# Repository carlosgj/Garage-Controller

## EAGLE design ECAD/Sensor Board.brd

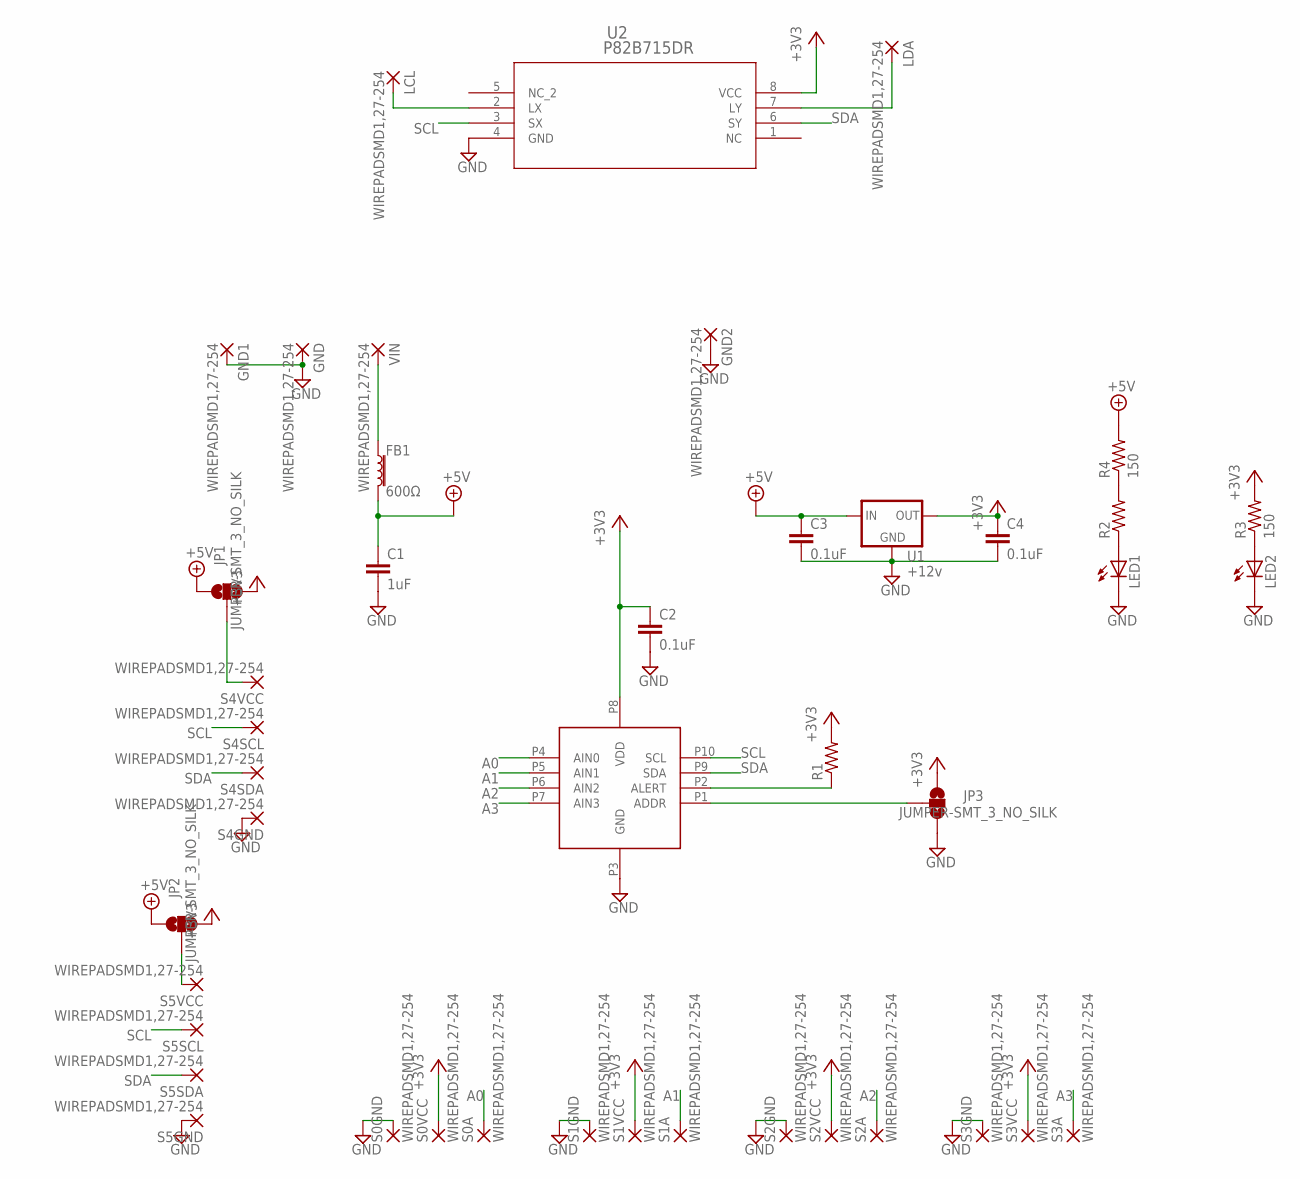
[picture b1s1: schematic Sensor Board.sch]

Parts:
C1: 1uF; C0805
C2, C3, C4: 0.1uF; C0805
FB1: 600Ω; 0805
GND, GND1, GND2: WIREPADSMD1,27-254; SMD1,27-2,54
JP1, JP2, JP3: JUMPER-SMT_3_NO_SILK; SMT-JUMPER_3_NO_SILK
LCL: WIREPADSMD1,27-254; SMD1,27-2,54
LDA: WIREPADSMD1,27-254; SMD1,27-2,54
LED1, LED2: LEDCHIP-LED0805; CHIP-LED0805
R1, R2: R-US_R0805; R0805
R3, R4: 150; R0805
S0A, S0GND, S0VCC, S1A, S1GND, S1VCC, S2A, S2GND, S2VCC, S3A, S3GND, S3VCC, S4GND, S4SCL, S4SDA, S4VCC, S5GND, S5SCL, S5SDA, S5VCC: WIREPADSMD1,27-254; SMD1,27-2,54
U1: +12v; TO-252
U2: P82B715DR; SO-08
U3: ADS1115; VSSOP-10
VIN: WIREPADSMD1,27-254; SMD1,27-2,54

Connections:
+3V3: C2.1, C4.1, JP1.3, JP2.3, JP3.1, R1.2, R3.2, S0VCC.1, S1VCC.1, S2VCC.1, S3VCC.1, U1.2 (OUT), U2.8 (VCC), U3.P8 (VDD)
+5V: C1.1, C3.1, FB1.2, JP1.1, JP2.1, R4.2, U1.1 (IN)
A0: S0A.1, U3.P4 (AIN0)
A1: S1A.1, U3.P5 (AIN1)
A2: S2A.1, U3.P6 (AIN2)
A3: S3A.1, U3.P7 (AIN3)
GND: C1.2, C2.2, C3.2, C4.2, GND.1, GND1.1, GND2.1, JP3.3, LED1.C, LED2.C, S0GND.1, S1GND.1, S2GND.1, S3GND.1, S4GND.1, S5GND.1, U1.3 (GND), U2.4 (GND), U3.P3 (GND)
unnamed: R1.1, U3.P2 (ALERT)
unnamed: FB1.1, VIN.1
unnamed: JP2.2, S5VCC.1
unnamed: JP3.2, U3.P1 (ADDR)
unnamed: JP1.2, S4VCC.1
unnamed: LED1.A, R2.1
unnamed: LED2.A, R3.1
unnamed: R2.2, R4.1
unnamed: LDA.1, U2.7 (LY)
unnamed: LCL.1, U2.2 (LX)
SCL: S4SCL.1, S5SCL.1, U2.3 (SX), U3.P10 (SCL)
SDA: S4SDA.1, S5SDA.1, U2.6 (SY), U3.P9 (SDA)

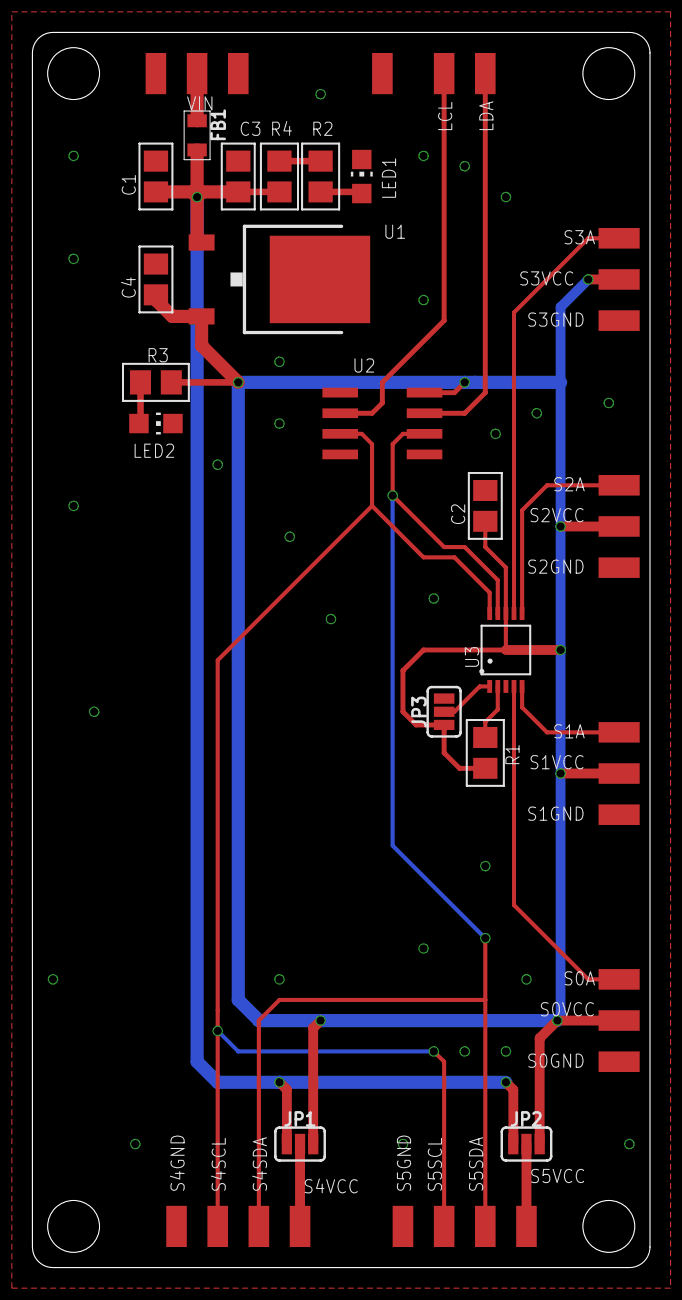
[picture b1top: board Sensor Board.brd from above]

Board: 2 copper layers, 38.1 x 76.2 mm, 43 parts (0 on the bottom side), 19 nets.

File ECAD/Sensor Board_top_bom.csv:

Comment,Designator,Footprint,LCSC Part #
,LED1 LED2,CHIP-LED0805,C84256
1k,R1,R0805,C17513
330,R2,R0805,C17630
+12v,U1,TO-252,C283274
0.1uF,C2 C3 C4,C0805,C49678
1uF,C1,C0805,C28323
150,R3 R4,R0805,C17471
ADS1115,U3,VSSOP-10,C37593
P82B715DR,U2,SO-08,C2649394

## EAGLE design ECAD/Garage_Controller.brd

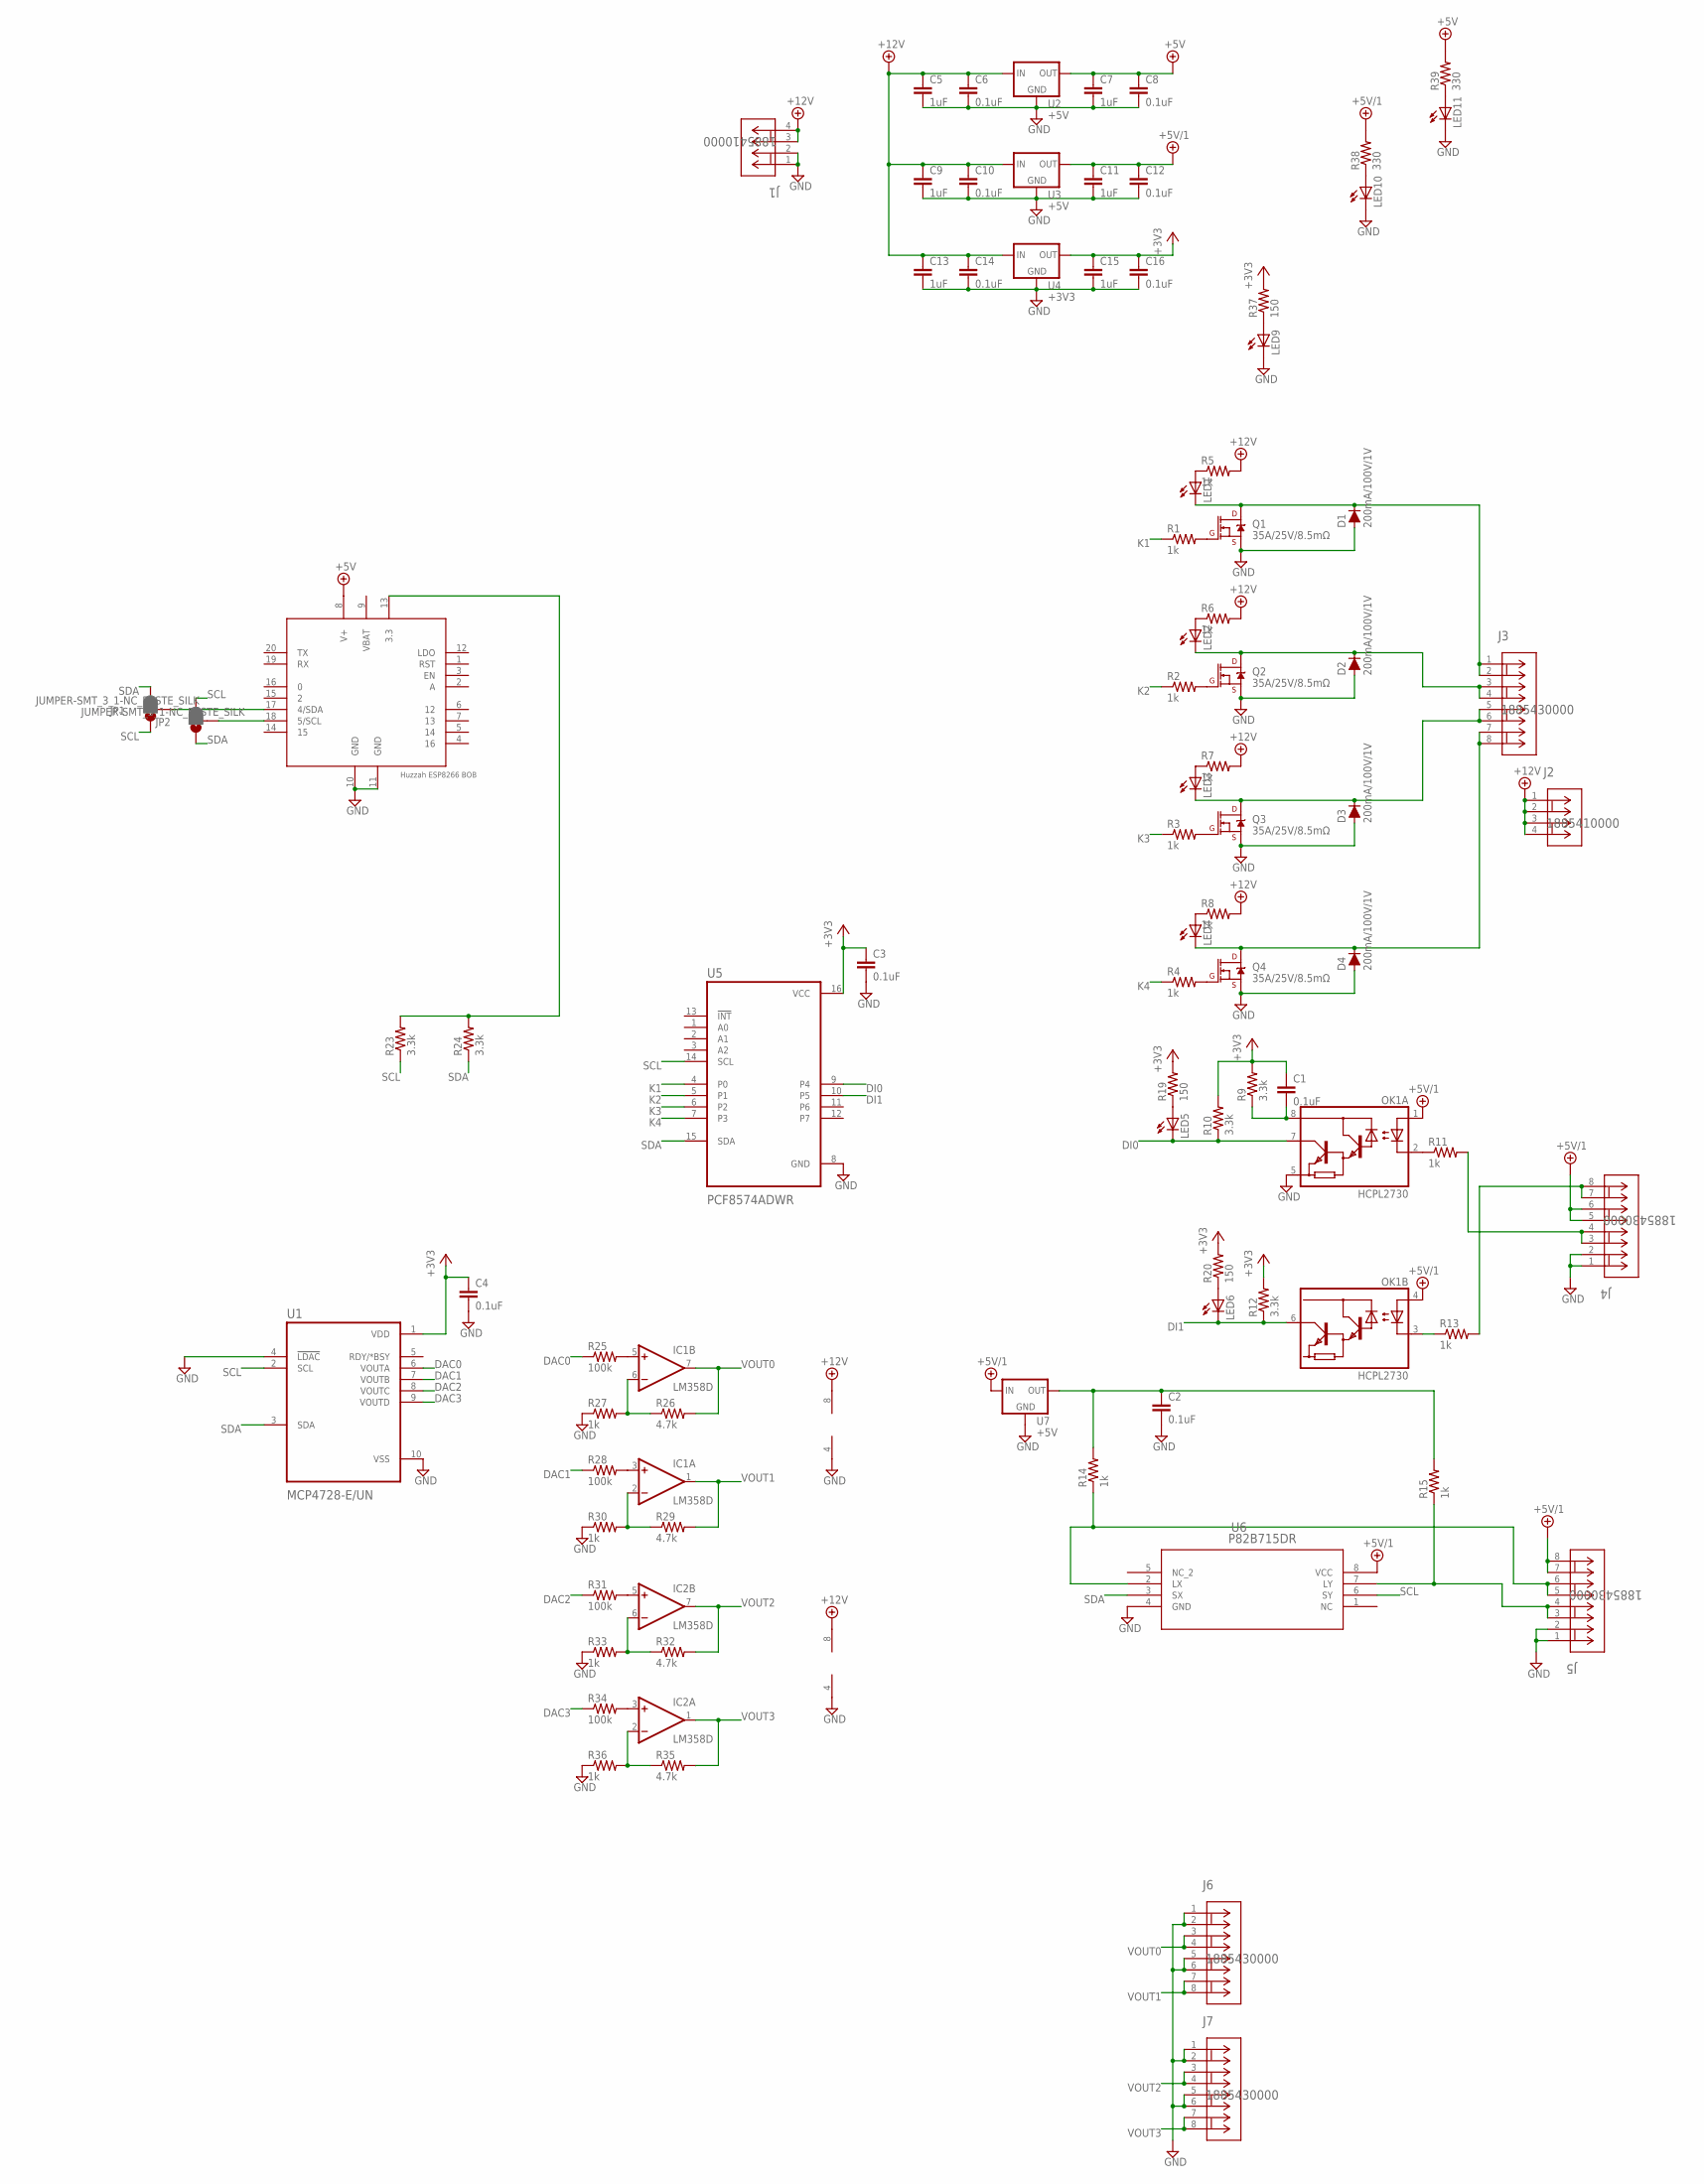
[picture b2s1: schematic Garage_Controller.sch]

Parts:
C1, C2, C3, C4, C6, C8, C10, C12, C14, C16: 0.1uF; C0805
C5, C7, C9, C11, C13, C15: 1uF; C0805
D1, D2, D3, D4: 200mA/100V/1V; DIODE-1N4148
IC1, IC2: LM358D; SO08
J1, J2: 1885410000; CONN_1885410000_WED
J3, J4, J5, J6, J7: 1885430000; CONN_1885430000_WED
JP1, JP2: JUMPER-SMT_3_1-NC_PASTE_SILK; SMT-JUMPER_3_1-NC_PASTE_SILK
LED1, LED2, LED3, LED4, LED5, LED6, LED9, LED10, LED11: LEDCHIP-LED0805; CHIP-LED0805
OK1: HCPL2730; DIL08
Q1, Q2, Q3, Q4: 35A/25V/8.5mΩ; TO-252/DPAK
R1, R2, R3, R4, R5, R6, R7, R8, R11, R13, R14, R15, R27, R30, R33, R36: 1k; R0805
R9, R10, R12, R23, R24: 3.3k; R0805
R19, R20, R37: 150; R0805
R25, R28, R31, R34: 100k; R0805
R26, R29, R32, R35: 4.7k; R0805
R38, R39: 330; R0805
U1: MCP4728-E/UN; SOP50P490X110-10N
U2, U3, U7: +5V; TO-252
U4: +3V3; TO-252
U5: PCF8574ADWR; SOIC127P1030X265-16N
U6: P82B715DR; SO-08
U$2: HUZZAH_ESP8266_BREAKOUT

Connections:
+3V3: C1.1, C3.1, C4.1, C15.1, C16.1, R9.2, R10.2, R12.2, R19.2, R20.2, R37.2, U1.1 (VDD), U4.2 (OUT), U5.16 (VCC)
+5V: C7.1, C8.1, R39.2, U2.2 (OUT), U$2.8 (V+)
+5V/1: C11.1, C12.1, J4.5, J4.6, J5.7, J5.8, OK1.1 (A1), OK1.4 (A2), R38.2, U3.2 (OUT), U6.8 (VCC), U7.1 (IN)
+12V: C5.1, C6.1, C9.1, C10.1, C13.1, C14.1, IC1.8 (V+), IC2.8 (V+), J1.3, J1.4, J2.1, J2.2, J2.3, J2.4, R5.2, R6.2, R7.2, R8.2, U2.1 (IN), U3.1 (IN), U4.1 (IN)
DAC0: R25.1, U1.6 (VOUTA)
DAC1: R28.1, U1.7 (VOUTB)
DAC2: R31.1, U1.8 (VOUTC)
DAC3: R34.1, U1.9 (VOUTD)
DI0: LED5.C, OK1.7 (VO1), R10.1, U5.9 (P4)
DI1: LED6.C, OK1.6 (VO2), R12.1, U5.10 (P5)
GND: C2.2, C3.2, C4.2, C5.2, C6.2, C7.2, C8.2, C9.2, C10.2, C11.2, C12.2, C13.2, C14.2, C15.2, C16.2, D1.A, D2.A, D3.A, D4.A, IC1.4 (V-), IC2.4 (V-), J1.1, J1.2, J4.1, J4.2, J5.1, J5.2, J6.1, J6.2, J6.5, J6.6, J7.1, J7.2, J7.5, J7.6, LED9.C, LED10.C, LED11.C, OK1.5 (GND), Q1.3 (S), Q2.3 (S), Q3.3 (S), Q4.3 (S), R27.1, R30.1, R33.1, R36.1, U1.4 (!LDAC), U1.10 (VSS), U2.3 (GND), U3.3 (GND), U4.3 (GND), U5.8 (GND), U6.4 (GND), U7.3 (GND), U$2.10 (GND), U$2.11 (GND)
K1: R1.1, U5.4 (P0)
K2: R2.1, U5.5 (P1)
K3: R3.1, U5.6 (P2)
K4: R4.1, U5.7 (P3)
unnamed: D1.C, J3.1, J3.2, LED1.C, Q1.2 (D)
unnamed: Q1.1 (G), R1.2
unnamed: D2.C, J3.3, J3.4, LED2.C, Q2.2 (D)
unnamed: Q2.1 (G), R2.2
unnamed: D3.C, J3.5, J3.6, LED3.C, Q3.2 (D)
unnamed: Q3.1 (G), R3.2
unnamed: D4.C, J3.7, J3.8, LED4.C, Q4.2 (D)
unnamed: Q4.1 (G), R4.2
unnamed: LED1.A, R5.1
unnamed: IC1.5 (+IN), R25.2
unnamed: LED2.A, R6.1
unnamed: LED3.A, R7.1
unnamed: J4.7, J4.8, R13.2
unnamed: LED4.A, R8.1
unnamed: C1.2, OK1.8 (VCC), R9.1
unnamed: IC1.6 (-IN), R26.1, R27.2
unnamed: OK1.2 (C1), R11.1
unnamed: IC1.3 (+IN), R28.2
unnamed: J4.3, J4.4, R11.2
unnamed: J5.5, J5.6, R14.1, U6.2 (LX)
unnamed: C2.1, R14.2, R15.2, U7.2 (OUT)
unnamed: IC1.2 (-IN), R29.1, R30.2
unnamed: J5.3, J5.4, R15.1, U6.7 (LY)
unnamed: OK1.3 (C2), R13.1
unnamed: LED5.A, R19.1
unnamed: LED6.A, R20.1
unnamed: IC2.5 (+IN), R31.2
unnamed: IC2.6 (-IN), R32.1, R33.2
unnamed: IC2.2 (-IN), R35.1, R36.2
unnamed: IC2.3 (+IN), R34.2
unnamed: R23.2, R24.2, U$2.13 (3.3)
unnamed: LED9.A, R37.1
unnamed: LED10.A, R38.1
unnamed: LED11.A, R39.1
unnamed: JP2.2, U$2.18 (5/SCL)
unnamed: JP1.2, U$2.17 (4/SDA)
SCL: JP1.1, JP2.3, R23.1, U1.2 (SCL), U5.14 (SCL), U6.6 (SY)
SDA: JP1.3, JP2.1, R24.1, U1.3 (SDA), U5.15 (SDA), U6.3 (SX)
VBAT: U$2.9 (VBAT)
VOUT0: IC1.7 (OUT), J6.3, J6.4, R26.2
VOUT1: IC1.1 (OUT), J6.7, J6.8, R29.2
VOUT2: IC2.7 (OUT), J7.3, J7.4, R32.2
VOUT3: IC2.1 (OUT), J7.7, J7.8, R35.2

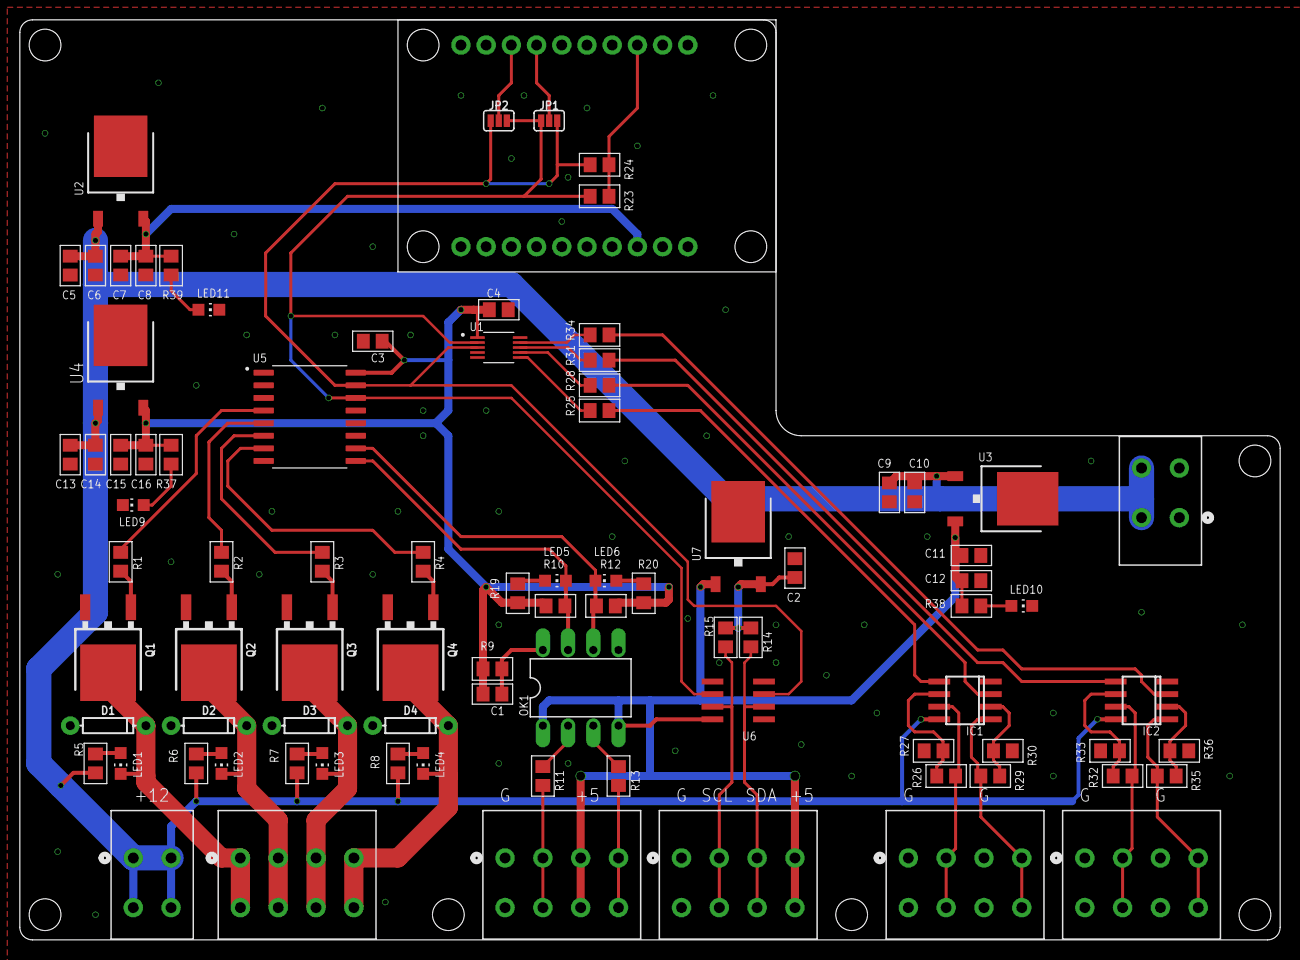
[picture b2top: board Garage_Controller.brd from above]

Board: 2 copper layers, 127.0 x 92.7 mm, 87 parts (0 on the bottom side), 57 nets.

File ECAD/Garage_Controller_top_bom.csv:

Comment,Designator,Footprint,LCSC Part #
,LED1 LED2 LED3 LED4 LED5 LED6 LED9 LED10 LED11,CHIP-LED0805,C84256
+3V3,U4,TO-252,C283274
+5V,U2 U3 U7,TO-252,C58069
0.1uF,C1 C2 C3 C4 C6 C8 C10 C12 C14 C16,C0805,C49678
1k,R1 R2 R3 R4 R5 R6 R7 R8 R11 R13 R14 R15 R27 R30 R33 R36,R0805,C17513
1uF,C5 C7 C9 C11 C13 C15,C0805,C28323
3.3k,R9 R10 R12 R23 R24,R0805,C26010
4.7k,R26 R29 R32 R35,R0805,C17673
35A/25V/8.5mΩ,Q1 Q2 Q3 Q4,TO-252/DPAK,C10668
100k,R25 R28 R31 R34,R0805,C149504
150,R19 R20 R37,R0805,C17471
330,R38 R39,R0805,C17630
LM358D,IC1 IC2,SO08,C7950
MCP4728-E/UN,U1,SOP50P490X110-10N,C478093
P82B715DR,U6,SO-08,C2649394
PCF8574ADWR,U5,SOIC127P1030X265-16N,C2867583

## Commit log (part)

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2026-06-24 Providing +5V at DI connector
2026-06-24 First work on ESPHome config
2026-06-24 gitignore
2026-06-24 Switching to Huzzah ESP8266 breakout
2026-06-27 Adding sensor board

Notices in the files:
parts and their libraries:
SparkFun-DiscreteSemi: Licensing: Creative Commons ShareAlike 4.0 International - https://creativecommons.org/licenses/by-sa/4.0
COPYRIGHT: Copyright (C) 2026 Ultra Librarian. All rights reserved.
